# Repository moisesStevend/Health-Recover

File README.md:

# Health-Recover
Proyecto Health Recover

_Desarrollo de un sistema de IoT para la adherencia a la terapia de
 rehabilitación en personas con ACV
 Laboratorio de Innovación en Salud - UPCH_

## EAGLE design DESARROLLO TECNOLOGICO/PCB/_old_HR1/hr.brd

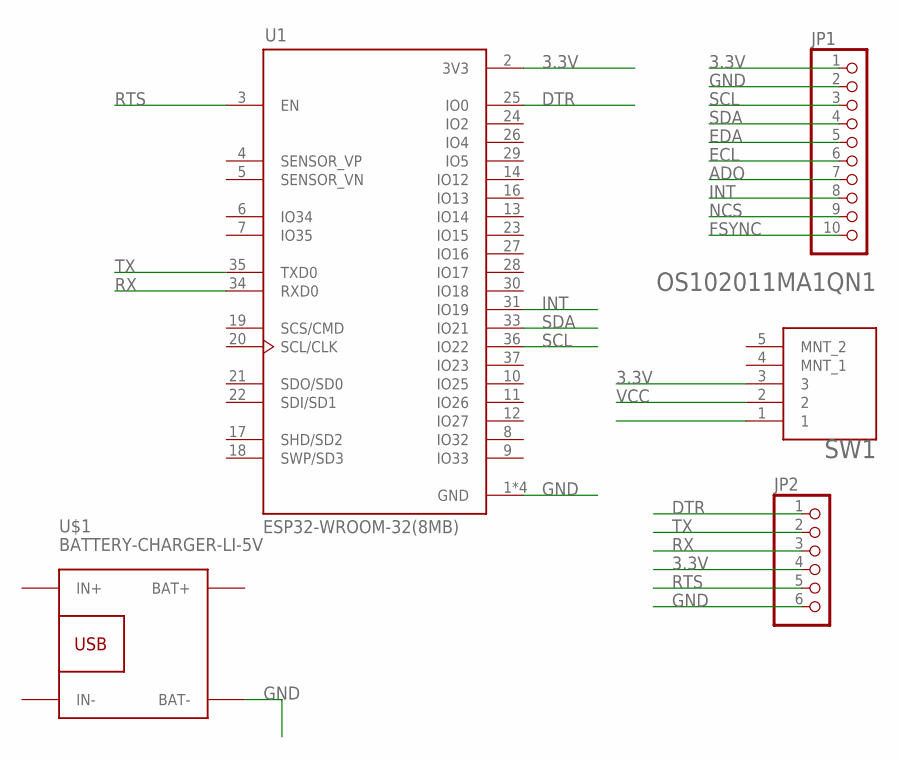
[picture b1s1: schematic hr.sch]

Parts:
JP1: PINHD-1X10; 1X10
JP2: PINHD-1X6; 1X06
SW1: C&K_OS102011MA1QN1C&K_OS102011MA1QN1_0_0; C&K_OS102011MA1QN1_0
U1: ESP32-WROOM-32(8MB); MODULE_ESP32-WROOM-32(8MB)
U$1: BATTERY-CHARGER-LI-5V

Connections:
3.3V: JP1.1, JP2.4, SW1.3, U1.2 (3V3)
ADO: JP1.7
DTR: JP2.1, U1.25 (IO0)
ECL: JP1.6
EDA: JP1.5
FSYNC: JP1.10
GND: JP1.2, JP2.6, U1.1 (GND), U1.15 (GND), U1.38 (GND), U1.39 (GND), U$1.BAT-
INT: JP1.8, U1.31 (IO19)
NCS: JP1.9
RTS: JP2.5, U1.3 (EN)
RX: JP2.3, U1.34 (RXD0)
SCL: JP1.3, U1.36 (IO22)
SDA: JP1.4, U1.33 (IO21)
TX: JP2.2, U1.35 (TXD0)
VCC: SW1.2

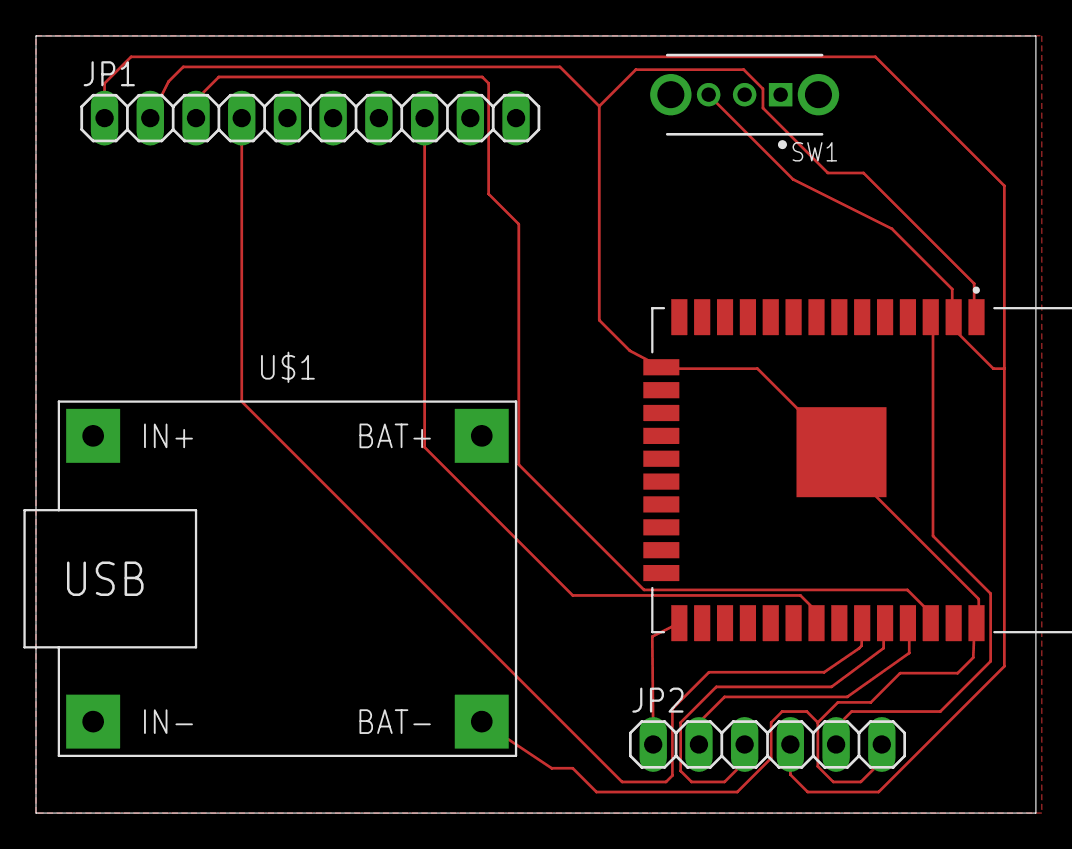
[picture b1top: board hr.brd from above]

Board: 2 copper layers, 55.5 x 43.2 mm, 5 parts (0 on the bottom side), 9 nets.

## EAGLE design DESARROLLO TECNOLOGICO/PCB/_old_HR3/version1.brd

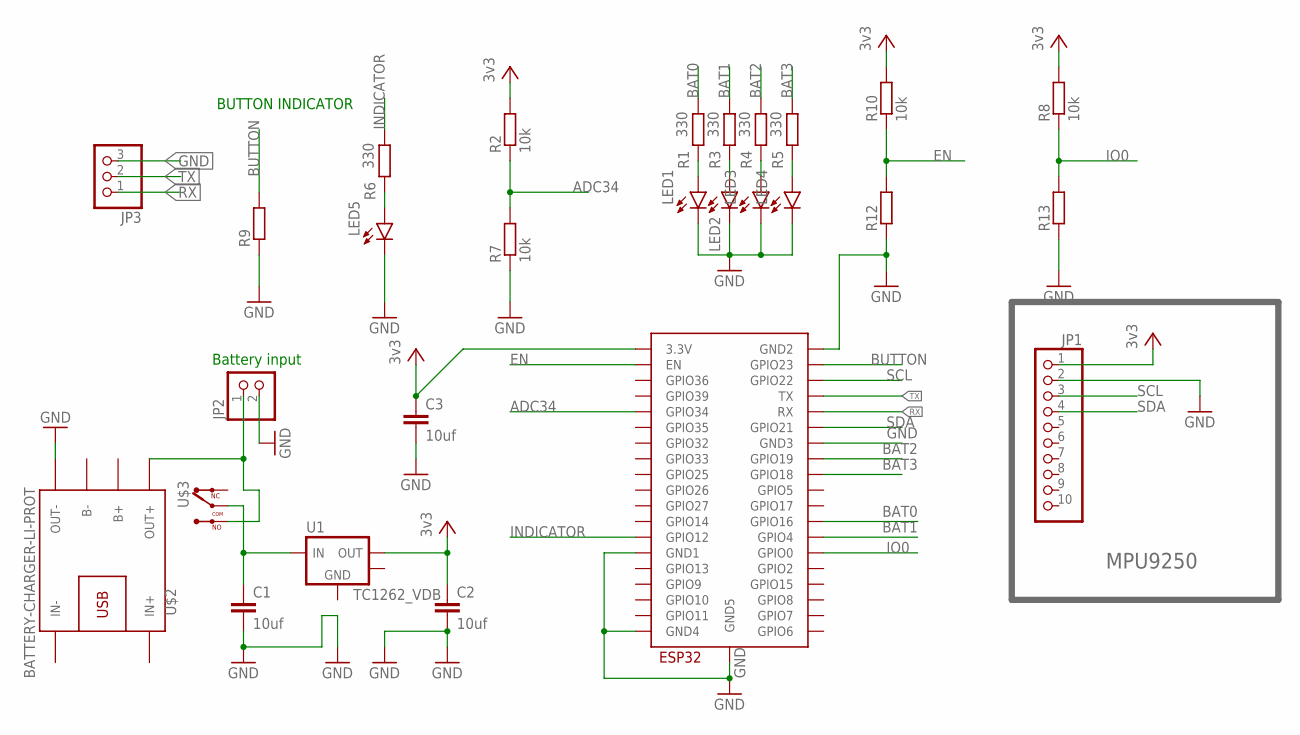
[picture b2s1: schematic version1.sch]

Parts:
C1, C2, C3: 10uf; C0805
JP1: PINHD-1X10_2.54-SMD-90°; 1X10SMD/90
JP2: PINHD-1X2; 1X02
JP3: PINHD-1X3; 1X03
LED1, LED2, LED3, LED4, LED5: LEDSML0805; SML0805
R1, R3, R4, R5, R6: 330; R0805
R2, R7, R8, R10: 10k; R0805
R9, R12, R13: R-EU_M2309; M2309
U1: TC1262_VDB; SOT-223-3
U$1: ESP32-WROOM
U$2: BATTERY-CHARGER-LI-PROT
U$3: -MICROSW; CON3

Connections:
ADC34: R2.1, R7.2, U$1.IO34 (GPIO34)
BAT0: R1.2, U$1.IO16 (GPIO16)
BAT1: R3.2, U$1.IO4 (GPIO4)
BAT2: R4.2, U$1.IO19 (GPIO19)
BAT3: R5.2, U$1.IO18 (GPIO18)
BUTTON: R9.2, U$1.IO23 (GPIO23)
EN: R10.1, R12.2, U$1.EN
GND: C1.2, C2.2, C3.2, JP1.2, JP2.2, JP3.3, LED1.C, LED2.C, LED3.C, LED4.C, LED5.C, R7.1, R9.1, R12.1, R13.1, U$1.GND1, U$1.GND2, U$1.GND3, U$1.GND4, U$1.GND5, U$2.OUT-
INDICATOR: R6.2, U$1.IO12 (GPIO12)
IO0: R8.1, R13.2, U$1.IO0 (GPIO0)
unnamed: LED5.A, R6.1
unnamed: JP2.1, U$2.OUT+, U$3.P$1, U$3.P$3
unnamed: LED1.A, R1.1
unnamed: LED2.A, R3.1
unnamed: LED3.A, R4.1
unnamed: LED4.A, R5.1
unnamed: C1.1, U1.1 (VIN), U$3.P$2
RX: JP3.1, U$1.RX
SCL: JP1.3, U$1.IO22 (GPIO22)
SDA: JP1.4, U$1.IO21 (GPIO21)
TAB: U1.2 (GND), U1.4 (TAB)
TX: JP3.2, U$1.TX
VCC: C2.1, C3.1, JP1.1, R2.2, R8.2, R10.2, U1.3 (VOUT), U$1.3V3 (3.3V)

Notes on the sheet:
Battery input
BUTTON INDICATOR
MPU9250

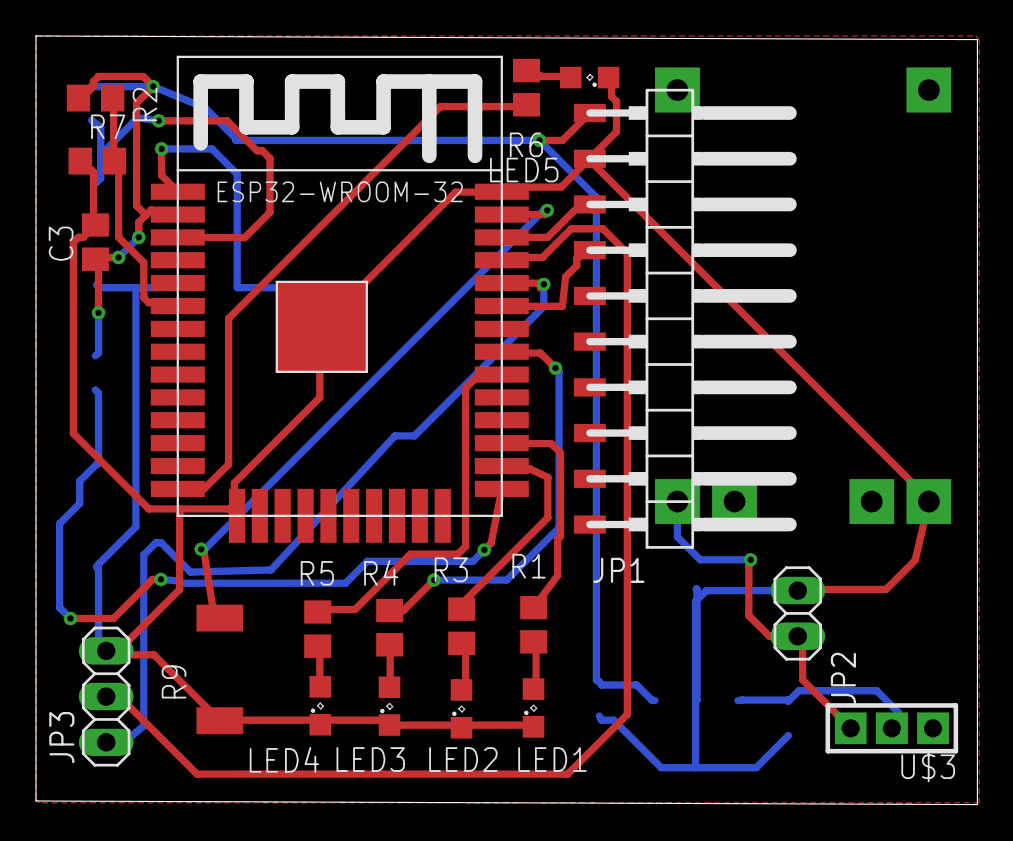
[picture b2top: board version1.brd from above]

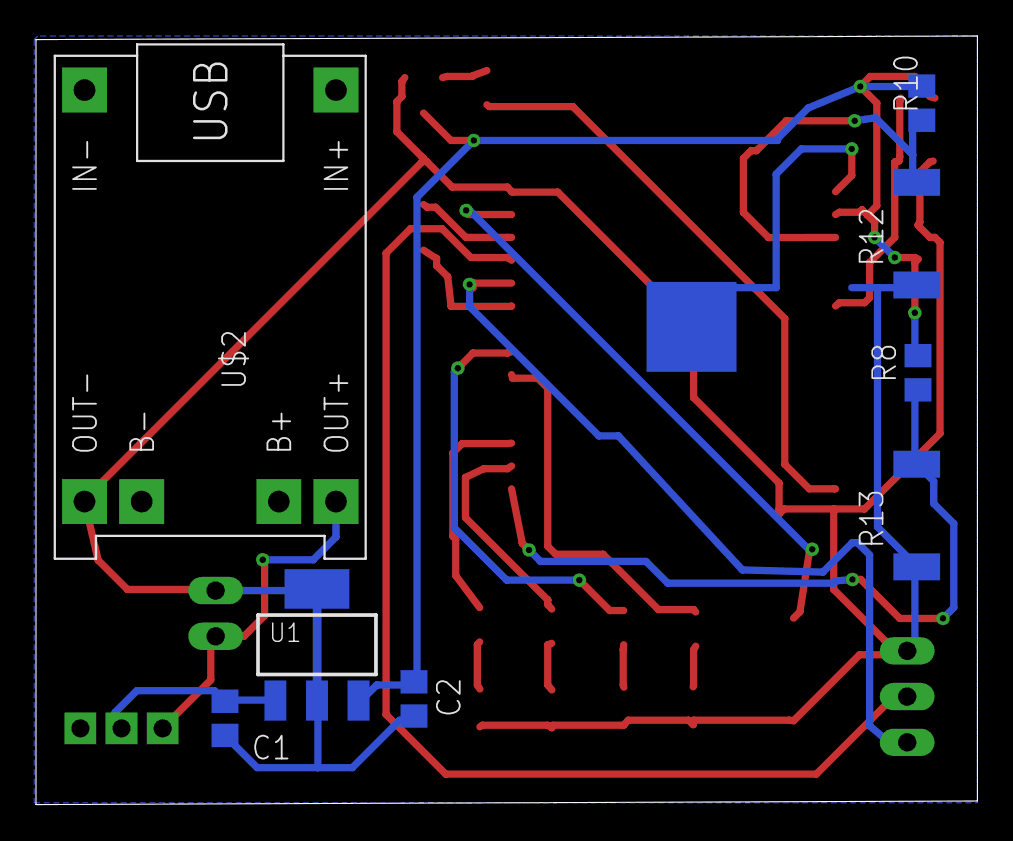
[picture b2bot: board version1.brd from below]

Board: 2 copper layers, 52.3 x 42.7 mm, 27 parts (8 on the bottom side), 23 nets.

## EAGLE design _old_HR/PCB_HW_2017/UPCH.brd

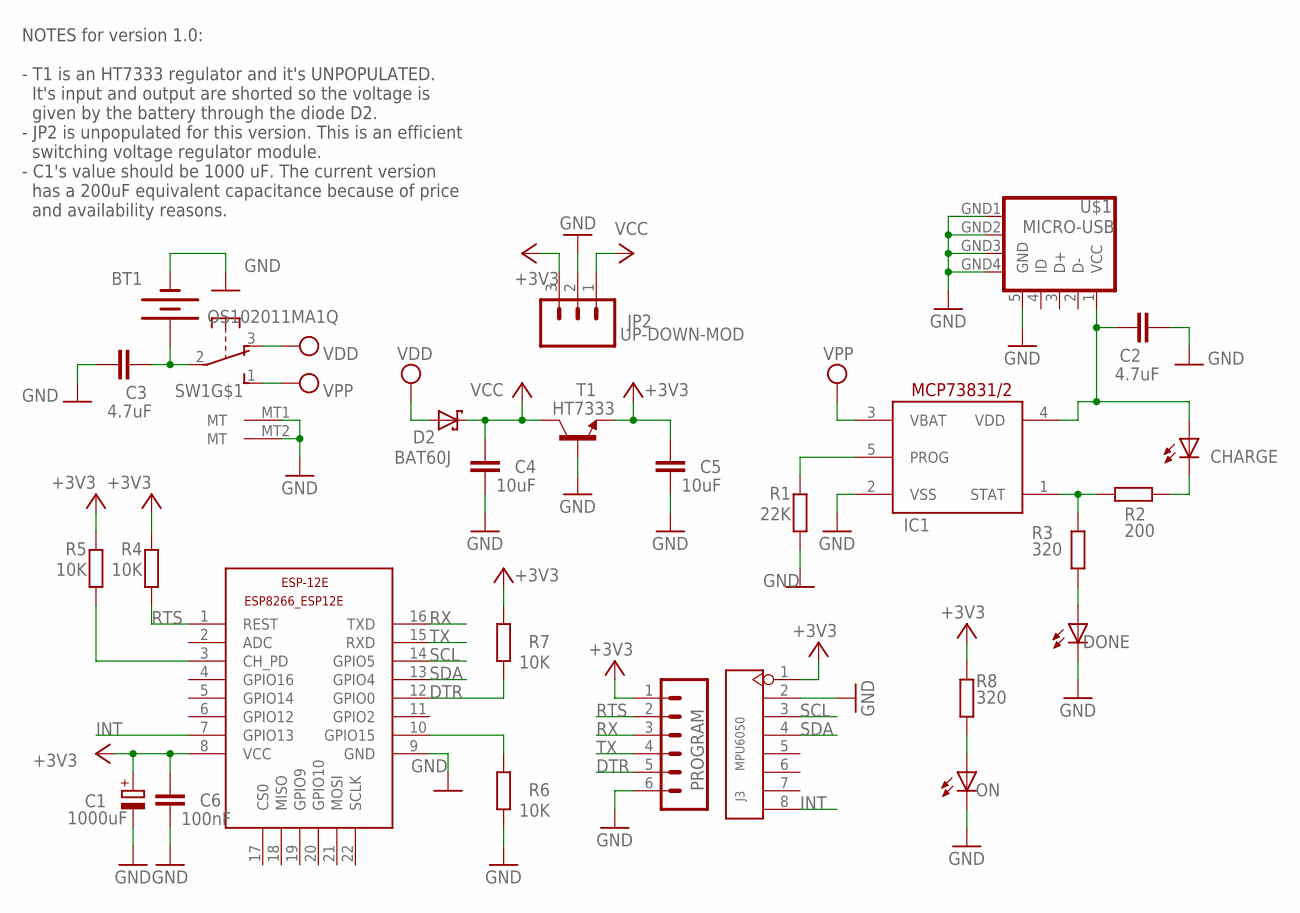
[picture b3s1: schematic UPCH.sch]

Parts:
BT1: BATTERY24.5MM; BATTCON_24.5MM
C1: 1000uF; D/7343-31W
C2, C3: 4.7uF; C1206
C4, C5: 10uF; C1206
C6: 100nF; C1206
CHARGE: LEDCHIP-LED0603; CHIP-LED0603
D2: BAT60J; SOD323_ST
DONE: LEDCHIP-LED0603; CHIP-LED0603
ESP-12E: ESP8266-12EESP8266-ESP12E; ESP8266-ESP12E
IC1: MCP73831; SOT23-5L
J3: MPU6050; H8-SMD-2.54-90D
JP2: UP-DOWN-MOD; 1X03
ON: LEDCHIP-LED0603; CHIP-LED0603
PROGRAM: CONN_06SILK_FEMALE_PTH; 1X06
R1: 22K; R0603
R2: 200; R1206
R3, R8: 320; R0603
R4, R5, R6: 10K; R0603
R7: 10K; R1206
SW1: OS102011MA1Q
T1: HT7333; SOT89-BCE
U$1: MICRO-USB

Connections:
+3V3: C1.+, C5.1, C6.1, ESP-12E.8 (VCC), J3.1, JP2.3, PROGRAM.1, R4.2, R5.2, R7.2, R8.1, T1.E
DTR: ESP-12E.12 (GPIO0), PROGRAM.5, R7.1
GND: BT1.2 (-), C1.-, C2.2, C3.2, C4.2, C5.2, C6.2, DONE.C, ESP-12E.9 (GND), IC1.2 (VSS), J3.2, JP2.2, ON.C, PROGRAM.6, R1.1, R6.1, SW1.MT1 (MT), SW1.MT2 (MT), T1.B, U$1.5 (GND), U$1.GND1 (GND), U$1.GND2 (GND), U$1.GND3 (GND), U$1.GND4 (GND)
INT: ESP-12E.7 (GPIO13), J3.8
unnamed: DONE.A, R3.2
unnamed: IC1.5 (PROG), R1.2
unnamed: CHARGE.C, R2.2
unnamed: BT1.1 (+), C3.1, SW1.2
unnamed: IC1.1 (STAT), R2.1, R3.1
unnamed: ESP-12E.3 (CH_PD), R5.1
unnamed: ESP-12E.10 (GPIO15), R6.2
unnamed: ON.A, R8.2
unnamed: C2.1, CHARGE.A, IC1.4 (VDD), U$1.1 (VCC)
RTS: ESP-12E.1 (REST), PROGRAM.2, R4.1
RX: ESP-12E.16 (TXD), PROGRAM.3
SCL: ESP-12E.14 (GPIO5), J3.3
SDA: ESP-12E.13 (GPIO4), J3.4
TX: ESP-12E.15 (RXD), PROGRAM.4
VCC: C4.1, D2.C, JP2.1, T1.C
VDD: D2.A, SW1.3 (O)
VPP: IC1.3 (VBAT), SW1.1 (S)

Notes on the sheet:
NOTES for version 1.0: - T1 is an HT7333 regulator and it's UNPOPULATED. It's input and output are shorted so the voltage is given by the battery through the diode D2. - JP2 is unpopulated for this version. This is an efficient switching voltage regulator module. - C1's value should be 1000 uF. The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

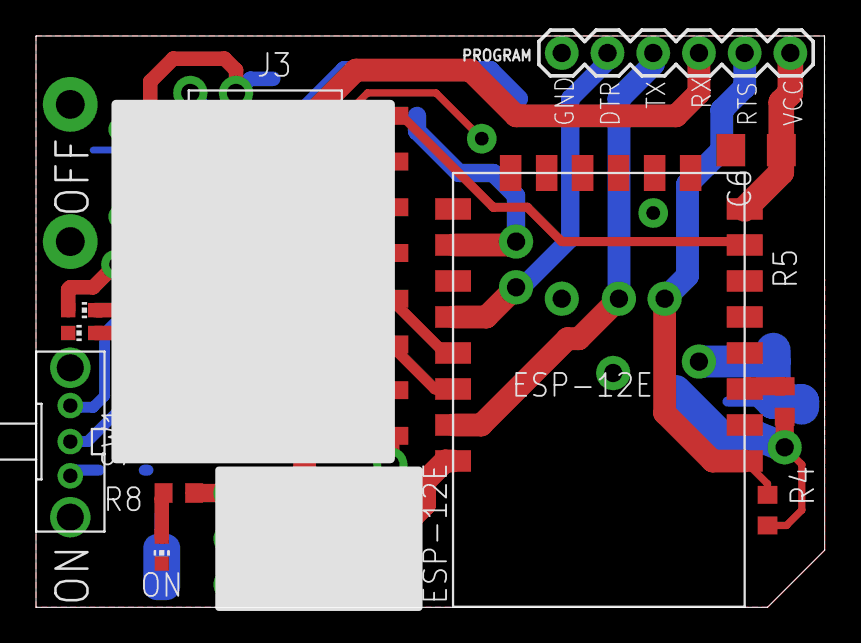
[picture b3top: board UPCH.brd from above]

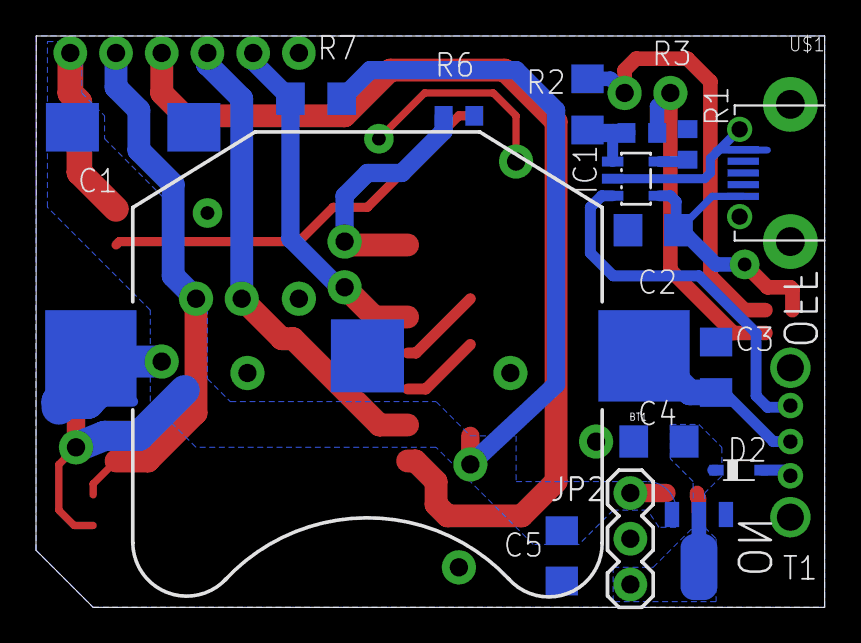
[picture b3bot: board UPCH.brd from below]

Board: 2 copper layers, 43.8 x 31.7 mm, 27 parts (16 on the bottom side), 21 nets.

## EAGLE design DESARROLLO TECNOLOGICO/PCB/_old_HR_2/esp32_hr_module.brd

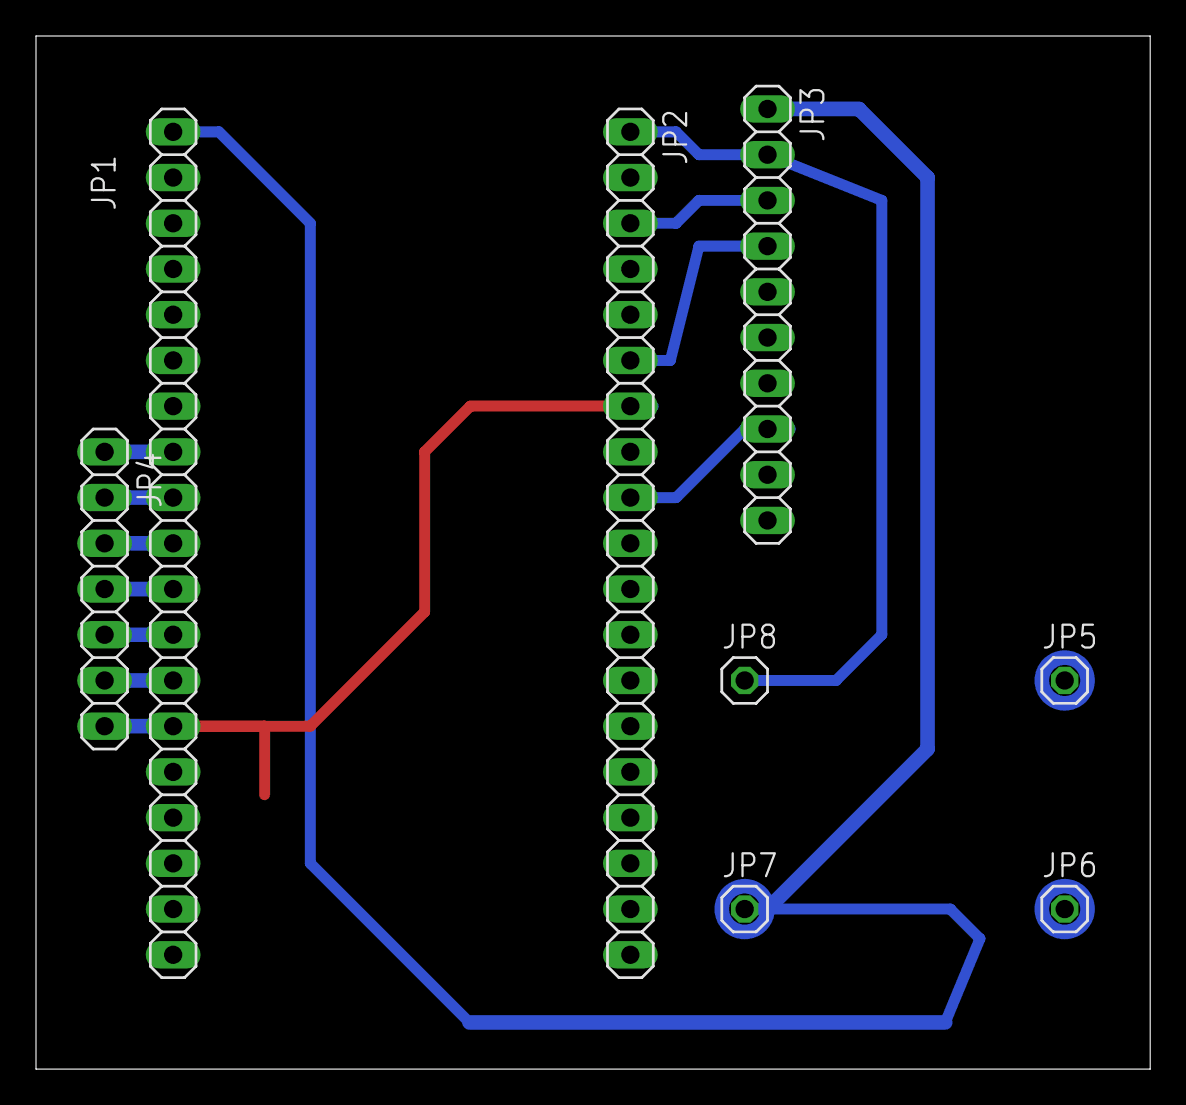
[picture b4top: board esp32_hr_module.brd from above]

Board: 2 copper layers, 61.9 x 57.4 mm, 8 parts (0 on the bottom side), 11 nets.

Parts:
JP1, JP2: 1X19
JP3: 1X10
JP4: 1X07
JP5, JP6, JP7, JP8: 1X01

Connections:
3V3: JP1.1, JP3.1, JP7.1
GND: JP1.14, JP1.18, JP2.1, JP2.7, JP3.2, JP4.7, JP8.1
INT: JP2.9, JP3.8
LED1: JP1.8, JP4.1
LED2: JP1.9, JP4.2
LED3: JP1.10, JP4.3
LED4: JP1.11, JP4.4
LED5: JP1.12, JP4.5
LED6: JP1.13, JP4.6
SCL: JP2.3, JP3.3
SDA: JP2.6, JP3.4

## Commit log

2020-05-18 codigos HR
2020-05-18 design layout and schematic
2020-05-19 Fotos y diseños
2020-05-19 new photos
2020-05-19 Conjunto mano-HR
2020-05-19 foto2
2020-05-22 adding documents and quotations
2020-06-15 adding directory with libraries
2020-06-16 new documents
2020-06-16 reestructuración de archivos
2020-06-24 add new features

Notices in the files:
parts and their libraries:
diy-modules: Released under the Creative Commons Attribution 4.0 International License: http://creativecommons.org/licenses/by/4.0
SparkFun: Licensing: CC v3.0 Share-Alike You are welcome to use this library for commercial purposes.
